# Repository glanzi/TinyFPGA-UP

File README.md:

# TinyFPGA-UP

The TinyFPGA UP board is a tiny FPGA board based on a ICE40UP5K-SG48 FPGA from Lattice.

This board is based on Luke Valenty's [TinyFPGA-BX](https://github.com/tinyfpga/TinyFPGA-BX) project.
The programming pins are compatible with Piotr Esden-Tempski's [iCEBreaker-bitsy](https://github.com/icebreaker-fpga/icebreaker) project.

WARNING: This is work in progress and not yet soldered nor tested!

## License
The TinyFPGA UP project is an open source project licensed under CERN Open Hardware Licence v1.2. Please see the included LICENSE file for details. If you do wish to distribute boards derived from this open source hardware project then you must also release the source files for the boards under CERN Open Hardware Licence v1.2. You are free to do this, but please improve upon the original design and provide a tangible benefit for users of the board.

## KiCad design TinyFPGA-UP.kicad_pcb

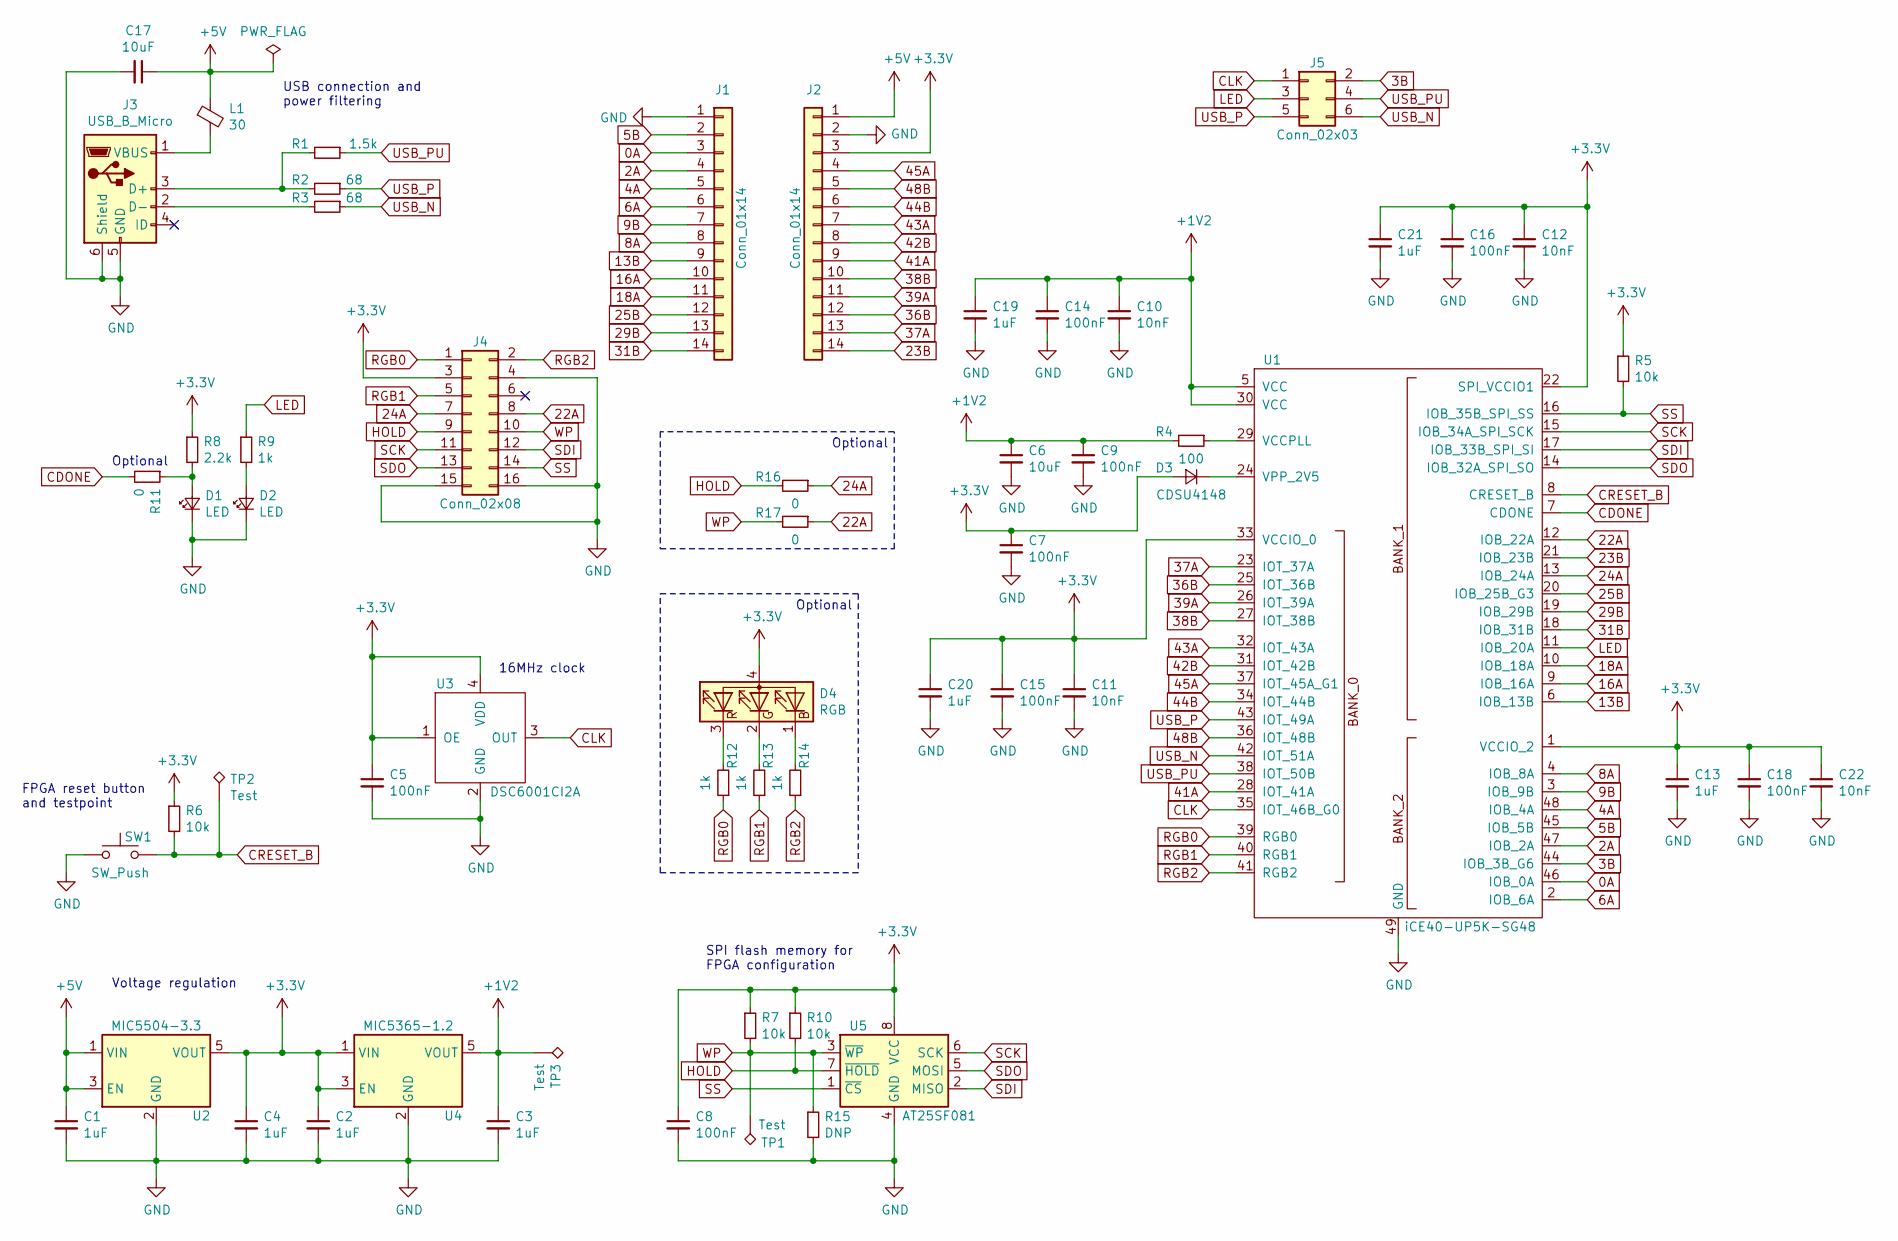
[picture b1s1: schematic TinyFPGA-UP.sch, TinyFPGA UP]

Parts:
C1, C2, C3, C4, C13, C19, C20, C21: 1uF; C_0402_1005Metric
C5, C7, C8, C9, C14, C15, C16, C18: 100nF; C_0402_1005Metric
C6: 10uF; C_0402_1005Metric
C10, C11, C12, C22: 10nF; C_0402_1005Metric
C17: 10uF; C_0603_1608Metric
D1, D2: LED; LED_0603_1608Metric
D3: CDSU4148; D_0603_1608Metric
D4: RGB; LTST-C19HE1WT
J1, J2: Conn_01x14; PinHeader_1x14_P2.54mm_Vertical
J3: USB_B_Micro; USB_Micro-B_Molex_47346-0001
J4: Conn_02x08; PinHeader_2x08_P2.54mm_Vertical_SMD
J5: Conn_02x03; PinHeader_2x03_P2.54mm_Vertical_SMD
L1: 30; L_0603_1608Metric
R1: 1.5k; R_0402_1005Metric
R2, R3: 68; R_0402_1005Metric
R4: 100; R_0402_1005Metric
R5, R6, R7, R10: 10k; R_0402_1005Metric
R8: 2.2k; R_0402_1005Metric
R9, R12, R13, R14: 1k; R_0402_1005Metric
R11, R16, R17: 0; R_0402_1005Metric
R15: DNP; R_0402_1005Metric
SW1: SW_Push; SW_SPST_PTS810
TP1, TP2, TP3: Test; TestPoint_Pad_D1.5mm
U1: iCE40-UP5K-SG48; QFN-48-1EP_7x7mm_P0.5mm_EP5.6x5.6mm
U2: MIC5504-3.3; SOT-23-5
U3: DSC6001CI2A; Crystal_SMD_3225-4Pin_3.2x2.5mm
U4: MIC5365-1.2; SOT-353_SC-70-5
U5: AT25SF081; SOIC-8_3.9x4.9mm_P1.27mm

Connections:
0A: J1.3, U1.46 (IOB_0A)
2A: J1.4, U1.47 (IOB_2A)
3B: J5.2, U1.44 (IOB_3B_G6)
4A: J1.5, U1.48 (IOB_4A)
5B: J1.2, U1.45 (IOB_5B)
6A: J1.6, U1.2 (IOB_6A)
8A: J1.8, U1.4 (IOB_8A)
9B: J1.7, U1.3 (IOB_9B)
13B: J1.9, U1.6 (IOB_13B)
16A: J1.10, U1.9 (IOB_16A)
18A: J1.11, U1.10 (IOB_18A)
22A: J4.8, R17.1, U1.12 (IOB_22A)
23B: J2.14, U1.21 (IOB_23B)
24A: J4.7, R16.1, U1.13 (IOB_24A)
25B: J1.12, U1.20 (IOB_25B_G3)
29B: J1.13, U1.19 (IOB_29B)
31B: J1.14, U1.18 (IOB_31B)
36B: J2.12, U1.25 (IOT_36B)
37A: J2.13, U1.23 (IOT_37A)
38B: J2.10, U1.27 (IOT_38B)
39A: J2.11, U1.26 (IOT_39A)
41A: J2.9, U1.28 (IOT_41A)
42B: J2.8, U1.31 (IOT_42B)
43A: J2.7, U1.32 (IOT_43A)
44B: J2.6, U1.34 (IOT_44B)
45A: J2.4, U1.37 (IOT_45A_G1)
48B: J2.5, U1.36 (IOT_48B)
+1V2: C3.1, C6.1, C9.1, C10.1, C14.1, C19.1, R4.2, TP3.1, U1.5 (VCC), U1.30 (VCC), U4.5 (VOUT)
+3V3: C2.1, C4.1, C5.1, C7.1, C8.1, C11.1, C12.1, C13.1, C15.1, C16.1, C18.1, C20.1, C21.1, C22.1, D3.2 (A), D4.4 (A), J2.3, J4.3, R5.1, R6.1, R7.1, R8.1, R10.1, U1.1 (VCCIO_2), U1.22 (SPI_VCCIO1), U1.33 (VCCIO_0), U2.5 (VOUT), U3.1 (OE), U3.4 (VDD), U4.1 (VIN), U4.3 (EN), U5.8 (VCC)
+5V: C1.1, C17.1, J2.1, L1.1, U2.1 (VIN), U2.3 (EN)
CDONE: R11.2, U1.7 (CDONE)
CLK: J5.1, U1.35 (IOT_46B_G0), U3.3 (OUT)
CRESET_B: R6.2, SW1.2, TP2.1, U1.8 (CRESET_B)
GND: C1.2, C2.2, C3.2, C4.2, C5.2, C6.2, C7.2, C8.2, C9.2, C10.2, C11.2, C12.2, C13.2, C14.2, C15.2, C16.2, C17.2, C18.2, C19.2, C20.2, C21.2, C22.2, D1.1 (K), D2.1 (K), J1.1, J2.2, J3.5 (GND), J3.6 (Shield), J4.4, J4.15, J4.16, R15.2, SW1.1, U1.49 (GND), U2.2 (GND), U3.2 (GND), U4.2 (GND), U5.4 (GND)
HOLD: J4.9, R10.2, R16.2, U5.7 (~HOLD)
LED: J5.3, R9.1, U1.11 (IOB_20A)
unnamed: D1.2 (A), R8.2, R11.1
unnamed: D2.2 (A), R9.2
unnamed: D3.1 (K), U1.24 (VPP_2V5)
unnamed: D4.1 (BK), R14.2
unnamed: D4.2 (GK), R13.2
unnamed: D4.3 (RK), R12.2
unnamed: J3.1 (VBUS), L1.2
unnamed: J3.2 (D-), R3.2
unnamed: J3.3 (D+), R1.2, R2.2
unnamed: R4.1, U1.29 (VCCPLL)
RGB0: J4.1, R12.1, U1.39 (RGB0)
RGB1: J4.5, R13.1, U1.40 (RGB1)
RGB2: J4.2, R14.1, U1.41 (RGB2)
SCK: J4.11, U1.15 (IOB_34A_SPI_SCK), U5.6 (SCK)
SDI: J4.12, U1.17 (IOB_33B_SPI_SI), U5.2 (MISO)
SDO: J4.13, U1.14 (IOB_32A_SPI_SO), U5.5 (MOSI)
SS: J4.14, R5.2, U1.16 (IOB_35B_SPI_SS), U5.1 (~CS)
USB_N: J5.6, R3.1, U1.42 (IOT_51A)
USB_P: J5.5, R2.1, U1.43 (IOT_49A)
USB_PU: J5.4, R1.1, U1.38 (IOT_50B)
WP: J4.10, R7.2, R15.1, R17.2, TP1.1, U5.3 (~WP)

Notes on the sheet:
USB connection and power filtering
Voltage regulation
16MHz clock
SPI flash memory for FPGA configuration
FPGA reset button and testpoint
Optional

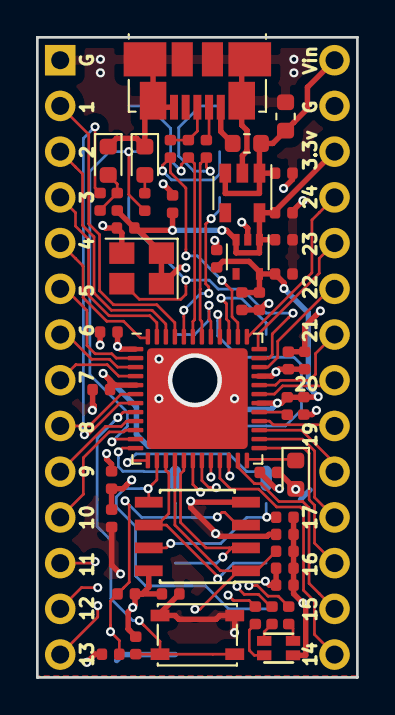
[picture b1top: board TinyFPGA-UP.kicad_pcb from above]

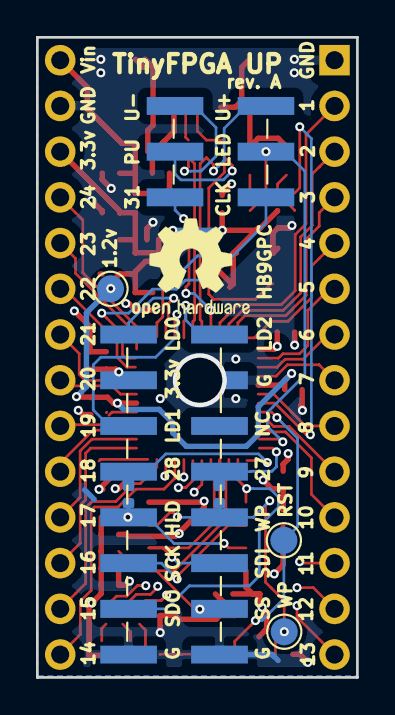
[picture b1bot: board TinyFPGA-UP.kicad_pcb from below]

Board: 4 copper layers, 17.8 x 35.6 mm, 58 parts (7 on the bottom side), 57 nets.

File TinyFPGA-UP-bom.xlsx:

Qty | Ref | MPN | Desc | Digi-Key | Mouser
1 | U1 | ICE40UP5K-SG48I | FPGA | 220-2212-1-ND
1 | U2 | MIC5504-3.3YM5-TR | 3.3v LDO | 576-4764-1-ND
1 | U3 | DSC6001CI2A-016.0000 | 16Mhz Clock | DSC6001CI2A-016.0000-ND
1 | U4 | MIC5365-1.2YC5-TR | 1.2v LDO | 576-3175-1-ND‎
1 | U5 | AT25SF081-SSHD-B | 4MBit SPI Flash | 1265-1176-5-ND
1 | J3 | 10118192-0001LF | USB Micro Connector | 609-4613-1-ND
1 | D4 | LTST-C19HE1WT | Led RGB | 160-2162-1-ND
1 | SW1 | PTS810 SJM 250 SMTR LFS | Reset/Program Button | CKN10502CT-ND
1 | L1 | BLM18PG300SN1D | Ferrite Bead, 30ohm@100MHz impedance, 50mOhm DC resistance , 0603 | 490-1035-1-ND
1 | D1 |  | Led Green, 0603
1 | D2 |  | Led Red, 0603
1 | D3 | CDSU4148 | Diode 75V 150MA 0603 (CDSU4148 or CDBU0520) | 641-1001-1-ND
1 | C17 |  | 10uF Ceramic Capacitor, 6.3V, X5R, 20%, 0603 | 1276-6775-1-ND‎
1 | C6 |  | 10uF Ceramic Capacitor, 6.3V, X5R, 20%, 0402 | 490-13211-1-ND‎
8 | C1, C2, C3, C4, C13, C19, C20, C21 |  | 1uF Ceramic Capacitor, 10V, X7R, 10%, 0402 | 587-2477-1-ND‎
8 | C5, C7, C8, C9, C14, C15, C16, C18 |  | 100nF Ceramic Capacitor, 25V, X5R, 10%, 0402 (0.1uF) | 1276-1001-1-ND‎
4 | C10, C11, C12, C22 |  | 10nF Ceramic Capacitor, 50V X7R, 10%, 0402 (10000pF) | 490-6043-1-ND‎
1 | R1 |  | 1.5k resistor, 1% tolerance, 1/16 watt, 0402 | P1.50KLCT-ND
2 | R2, R3 |  | 68ohm resistor, 1% tolerance, 1/10 watt, 0402 | P68.0LCT-ND
1 | R4 |  | 100ohm resistor, 1% tolerance, 1/10 watt | P100LCT-ND
4 | R5, R6, R7, R10 |  | 10k resistor, 1% tolerance, 1/16 watt, 0402 | P10.0KLCT-ND
1 | R8 |  | 2.2k, 0402 (spez.) | P2.20KLCT-ND
4 | R9, R12, R13, R14 |  | 1k resistor, 1% tolerance, 1/16 watt, 0402 | P1.00KLCT-ND
1 | R11 |  | 0ohm resistor, bridge, 1/10 watt, 0402 | P0.0JCT-ND
 | R15, R16, R17 |  | DNP

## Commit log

2018-11-15 Update routing
2018-11-16 Make LED, WP, HLC compatible
2018-11-16 Adding plots
2018-11-16 Add BOM
2018-11-16 Minor changes
2018-11-16 Add comments
2018-11-16 Add more comments
2018-11-17 Fix Pads Mask Clearance
2019-09-22 Simplify hand soldering
2019-09-22 Remove old plots
